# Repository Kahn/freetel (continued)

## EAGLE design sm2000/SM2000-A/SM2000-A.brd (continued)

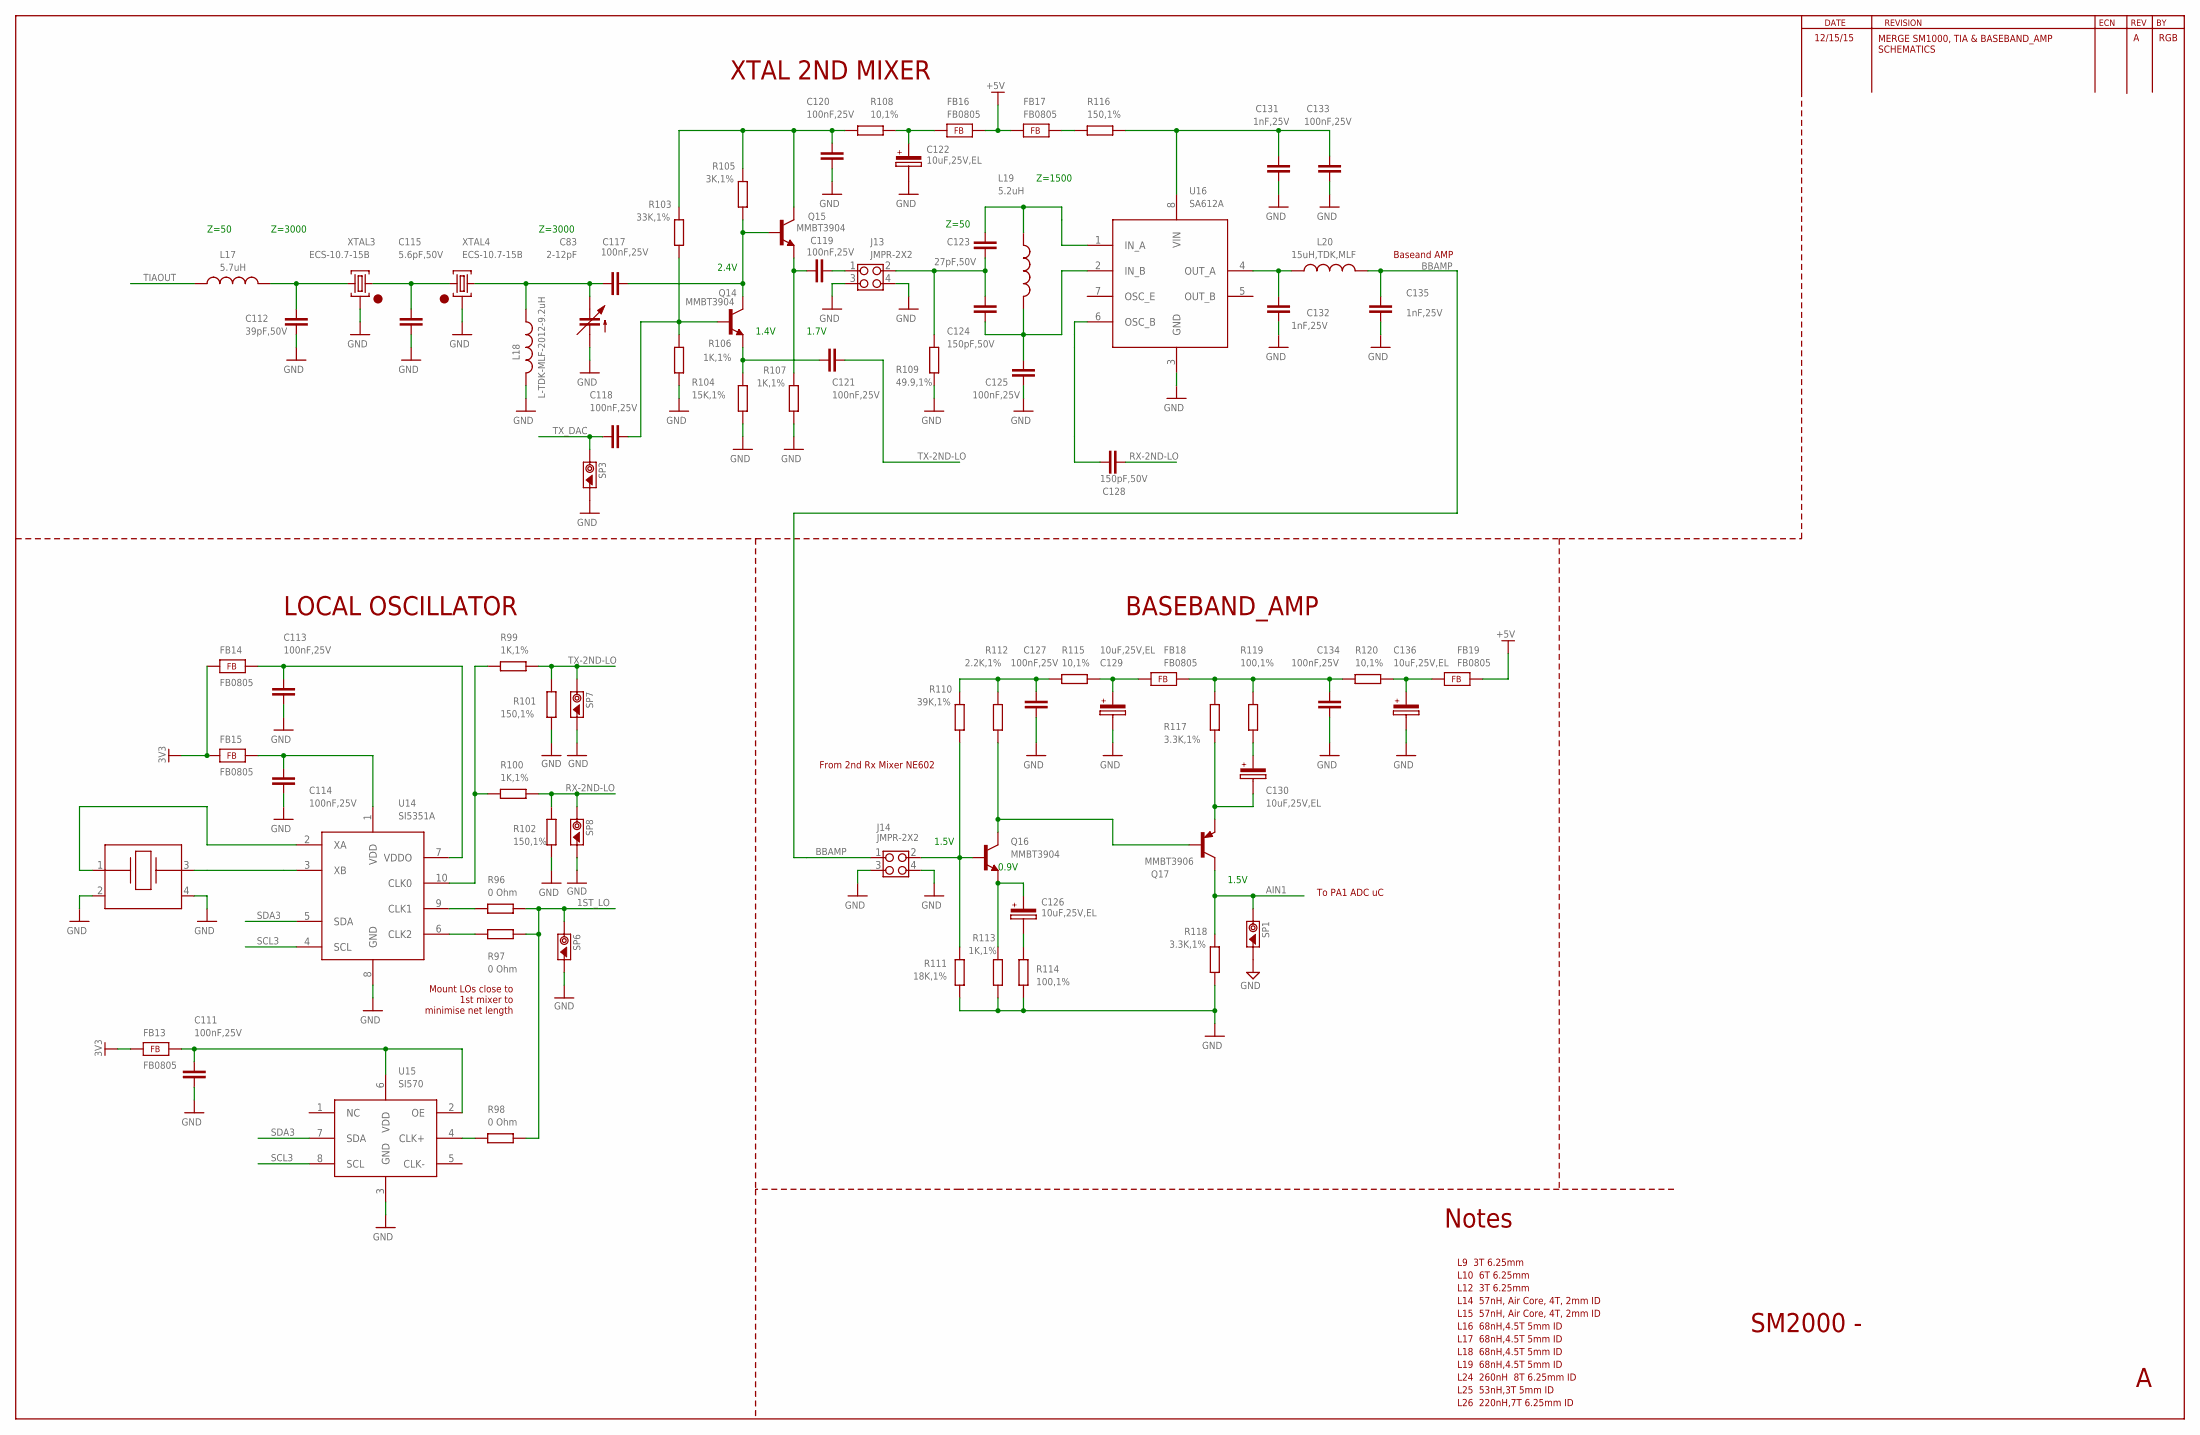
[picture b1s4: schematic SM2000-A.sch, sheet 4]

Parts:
C83: 2-12pF; TRIMCAP_VAR_2222_V
C111, C113, C114, C117, C118, C119, C120, C121, C125, C127, C133, C134: 100nF,25V; C0805
C112: 39pF,50V; C0805
C115: 5.6pF,50V; C0805
C122, C126, C129, C130, C136: 10uF,25V,EL; NICHICON-WJ-5
C123: 27pF,50V; C0805
C124, C128: 150pF,50V; C0805
C131, C132, C135: 1nF,25V; C0805
FB13, FB14, FB15, FB16, FB17, FB18, FB19: FB0805; FE0805
J13, J14: JMPR-2X2; JMPR-2X2X.1
L17: 5.7uH; L-TDK-MLF2012
L18: L-TDK-MLF-2012-9.2uH; L-TDK-MLF2012
L19: 5.2uH; L-TDK-MLF2012
L20: 15uH,TDK,MLF; L-TDK-MLF2012
Q14, Q15, Q16: MMBT3904; SOT23
Q17: MMBT3906; SOT23
R96, R97, R98: 0 Ohm; R0805
R99, R100, R106, R107, R113: 1K,1%; R0805
R101, R102, R116: 150,1%; R0805
R103: 33K,1%; R0805
R104: 15K,1%; R0805
R105: 3K,1%; R0805
R108, R115, R120: 10,1%; R0805
R109: 49.9,1%; R0805
R110: 39K,1%; R0805
R111: 18K,1%; R0805
R112: 2.2K,1%; R0805
R114, R119: 100,1%; R0805
R117, R118: 3.3K,1%; R0805
SP1, SP3, SP6, SP7, SP8: SCOPE_PAD
U14: SI5351A; MSOP10
U15: SI570
U16: SA612A; SO-08
XTAL2: 25.000MHz; CTS-405
XTAL3, XTAL4: ECS-10.7-15B; HC49U

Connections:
1ST_LO: R96.1, R97.1, R98.1, SP6.1; also elsewhere on the board
3V3: FB13.1, FB14.1, FB15.1; also elsewhere on the board
+5V: FB16.2, FB17.1, FB19.2; also elsewhere on the board
AIN1: Q17.3 (C), R118.2, SP1.1; also elsewhere on the board
BBAMP: C135.2, J14.1, L20.P$2 (2)
GND: C83.S, C111.2, C112.2, C113.2, C114.2, C115.2, C120.2, C122.2, C125.1, C127.2, C129.2, C131.1, C132.1, C133.1, C134.2, C135.1, C136.2, J13.3, J13.4, J14.3, J14.4, L18.P$2 (2), R101.2, R102.2, R104.1, R106.1, R107.1, R109.1, R111.1, R113.1, R114.1, R118.1, SP1.2, SP3.2, SP6.2, SP7.2, SP8.2, U14.8 (GND), U15.3 (GND), U16.3 (GND), XTAL2.2, XTAL2.4, XTAL3.2, XTAL4.2; also elsewhere on the board
unnamed: U14.2 (XA), XTAL2.1
unnamed: C119.2, J13.1
unnamed: C114.1, FB15.2, U14.1 (VDD)
unnamed: C123.1, C124.2, J13.2, R109.2
unnamed: C124.1, C125.2, L19.P$2 (2), U16.2 (IN_B)
unnamed: U14.3 (XB), XTAL2.3
unnamed: C126.1, Q16.2 (E), R113.2
unnamed: C134.1, FB18.2, R117.2, R119.2, R120.2
unnamed: C127.1, R110.2, R112.2, R115.2
unnamed: J14.2, Q16.1 (B), R110.1, R111.2
unnamed: Q16.3 (C), Q17.1 (B), R112.1
unnamed: C130.2, Q17.2 (E), R117.1
unnamed: C129.1, FB18.1, R115.1
unnamed: C126.2, R114.2
unnamed: C130.1, R119.1
unnamed: C136.1, FB19.1, R120.1
unnamed: C111.1, FB13.2, U15.2 (OE), U15.6 (VDD)
unnamed: C113.1, FB14.2, U14.7 (VDDO)
unnamed: R96.2, U14.9 (CLK1)
unnamed: R97.2, U14.6 (CLK2)
unnamed: R98.2, U15.4 (CLK+)
unnamed: R99.2, R100.2, U14.10 (CLK0)
unnamed: C120.1, Q15.3 (C), R103.2, R105.2, R108.2
unnamed: C117.2, Q14.3 (C), Q15.1 (B), R105.1
unnamed: C122.1, FB16.1, R108.1
unnamed: C112.1, L17.P$2 (2), XTAL3.3
unnamed: C115.1, XTAL3.1, XTAL4.1
unnamed: C83.R1 (R), C83.R2 (R), C117.1, L18.P$1 (1), XTAL4.3
unnamed: C118.1, Q14.1 (B), R103.1, R104.2
unnamed: C121.1, Q14.2 (E), R106.2
unnamed: C119.1, Q15.2 (E), R107.2
unnamed: C123.2, L19.P$1 (1), U16.1 (IN_A)
unnamed: FB17.2, R116.2
unnamed: C131.2, C133.2, R116.1, U16.8 (VIN)
unnamed: C128.2, U16.6 (OSC_B)
unnamed: C132.2, L20.P$1 (1), U16.4 (OUT_A)
RX-2ND-LO: C128.1, R100.1, R102.1, SP8.1
SCL3: U14.4 (SCL), U15.8 (SCL); also elsewhere on the board
SDA3: U14.5 (SDA), U15.7 (SDA); also elsewhere on the board
TIAOUT: L17.P$1 (1); also elsewhere on the board
TX-2ND-LO: C121.2, R99.1, R101.1, SP7.1
TX_DAC: C118.2, SP3.1; also elsewhere on the board

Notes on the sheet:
12/15/15
MERGE SM1000, TIA & BASEBAND_AMP SCHEMATICS
RGB
SM2000 -
L10 6T 6.25mm
L12 3T 6.25mm
L9 3T 6.25mm
L26 220nH,7T 6.25mm ID
L19 68nH,4.5T 5mm ID
L18 68nH,4.5T 5mm ID
L17 68nH,4.5T 5mm ID
L16 68nH,4.5T 5mm ID
L24 260nH 8T 6.25mm ID
L25 53nH,3T 5mm ID
L15 57nH, Air Core, 4T, 2mm ID
L14 57nH, Air Core, 4T, 2mm ID
1.7V
1.4V
2.4V
Z=50
Z=3000
Z=1500
Baseand AMP
XTAL 2ND MIXER
Notes
To PA1 ADC uC
From 2nd Rx Mixer NE602
1.5V
0.9V
BASEBAND_AMP
Mount LOs close to 1st mixer to minimise net length
LOCAL OSCILLATOR

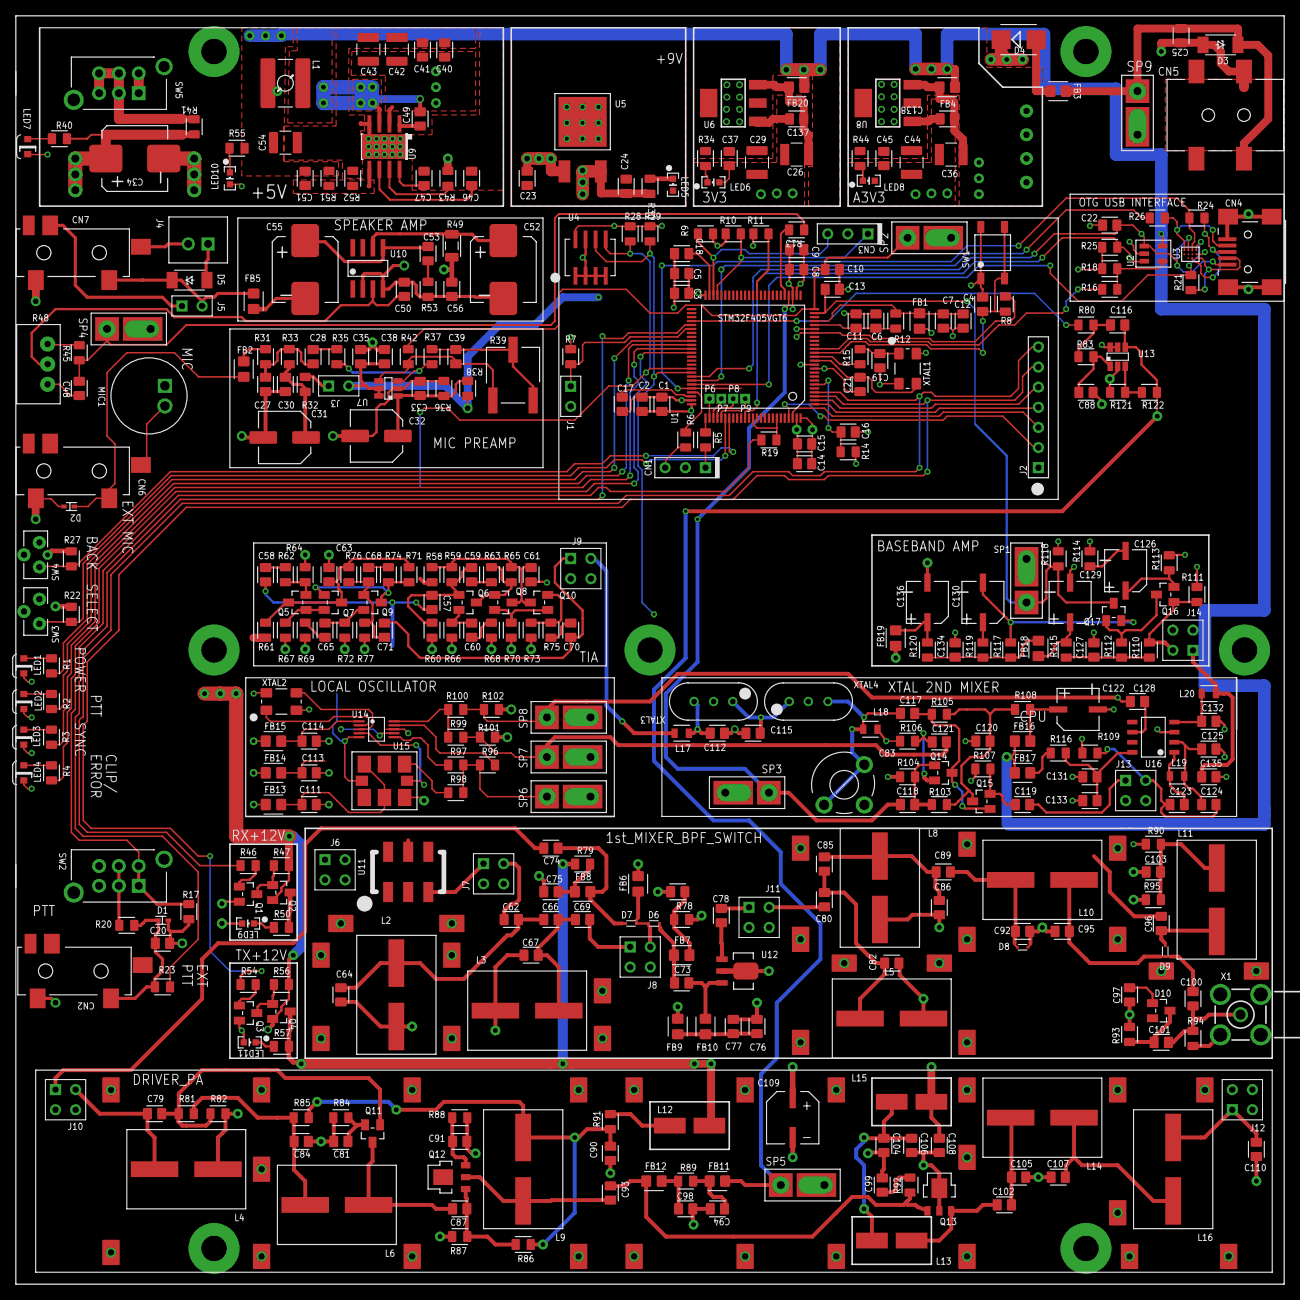
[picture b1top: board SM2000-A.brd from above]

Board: 4 copper layers, 160.0 x 160.0 mm, 452 parts (0 on the bottom side), 221 nets.

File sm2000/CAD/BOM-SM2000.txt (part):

Bill of Materials from SM2000.sch, 407 parts, grouped by values, as of 1/28/2016 6:16:19 PM

Part	Value			Device			Package
C1	100nF,25V		CAP-0805		C0805			
C3	100nF,25V		CAP-0805		C0805			
C4	100nF,25V		CAP-0805		C0805			
C8	100nF,25V		CAP-0805		C0805			
C11	100nF,25V		CAP-0805		C0805			
C12	100nF,25V		CAP-0805		C0805			
C14	100nF,25V		CAP-0805		C0805			
C20	100nF,25V		CAP-0805		C0805			
C24	100nF,25V		CAP-0805		C0805			
C30	100nF,25V		CAP-0805		C0805			
C33	100nF,25V		CAP-0805		C0805			
C35	100nF,25V		CAP-0805		C0805			
C37	100nF,25V		CAP-0805		C0805			
C41	100nF,25V		CAP-0805		C0805			
C45	100nF,25V		CAP-0805		C0805			
C48	100nF,25V		CAP-0805		C0805			
C49	100nF,25V		CAP-0805		C0805			
C56	100nF,25V		CAP-0805		C0805			
C57	100nF,25V		CAP-0805		C0805			
C58	100nF,25V		CAP-0805		C0805			
C59	100nF,25V		CAP-0805		C0805			
C60	100nF,25V		CAP-0805		C0805			
C61	100nF,25V		CAP-0805		C0805			
C63	100nF,25V		CAP-0805		C0805			
C65	100nF,25V		CAP-0805		C0805			
C68	100nF,25V		CAP-0805		C0805			
C70	100nF,25V		CAP-0805		C0805			
C71	100nF,25V		CAP-0805		C0805			
C137	100nF,25V		CAP-0805		C0805			
C138	100nF,25V		CAP-0805		C0805
C2	10nF,25V		CAP-0805		C0805			
C5	10nF,25V		CAP-0805		C0805			
C9	10nF,25V		CAP-0805		C0805			
C15	10nF,25V		CAP-0805		C0805			
C25	10nF,25V		CAP-0805		C0805
C6	1uF,25V			CAP-0805		C0805			
C7	1uF,25V			CAP-0805		C0805			
C77	1uF,25V			CAP-0805		C0805
C10	1nF,25V			CAP-0805		C0805			
C13	1nF,25V			CAP-0805		C0805			
C27	1nF,25V			CAP-0805		C0805			
C40	1nF,25V			CAP-0805		C0805			
C72	1nF,25V			CAP-0805		C0805			
C73	1nF,25V			CAP-0805		C0805			
C74	1nF,25V			CAP-0805		C0805			
C75	1nF,25V			CAP-0805		C0805			
C76	1nF,25V			CAP-0805		C0805			
C78	1nF,25V			CAP-0805		C0805			
C81	1nF,25V			CAP-0805		C0805			
C91	1nF,25V			CAP-0805		C0805			
C96	1nF,25V			CAP-0805		C0805			
C97	1nF,25V			CAP-0805		C0805			
C98	1nF,25V			CAP-0805		C0805			
C100	1nF,25V			CAP-0805		C0805			
C102	1nF,25V			CAP-0805		C0805			
C103	1nF,25V			CAP-0805		C0805			
C106	1nF,25V			CAP-0805		C0805			
C131	1nF,25V			CAP-0805		C0805			
C132	1nF,25V			CAP-0805		C0805			
C135	1nF,25V			CAP-0805		C0805
C16	1uF,16V			CAP-0805		C0805
C17	2.2uF,25V		CAP-0805		C0805			
C18	2.2uF,25V		CAP-0805		C0805			
C38	2.2uF,25V		CAP-0805		C0805
C19	20pF,50V		CAP-0805		C0805			
C21	20pF,50V		CAP-0805		C0805			
C51	20pF,50V		CAP-0805		C0805
C22	4.7uF,25V		CAP-0805		C0805
C23	.33uF,25V		CAP-0805		C0805
C26	22uF,25V		CAP-1210		C1210			
C29	22uF,25V		CAP-1210		C1210			
C36	22uF,25V		CAP-1210		C1210			
C42	22uF,25V		CAP-1210		C1210			
C43	22uF,25V		CAP-1210		C1210			
C44	22uF,25V		CAP-1210		C1210
C28	220nF,25V		CAP-0805		C0805
C31	100uF,6.3V,EL		NICHICON-WX-6.3		NICHICON-WX-6.3		
C32	100uF,6.3V,EL		NICHICON-WX-6.3		NICHICON-WX-6.3
C34	220uF,25V		CAP-CHEMI-MVE-HA0	CAP-CHEMI-HA0		
C52	220uF,25V		CAP-CHEMI-MVE-HA0	CAP-CHEMI-HA0		
C55	220uF,25V		CAP-CHEMI-MVE-HA0	CAP-CHEMI-HA0
C39	100pF,50V		CAP-0805		C0805
C46	470nF,25V		CAP-0805		C0805
C47	8.2nF,25V		CAP-0805		C0805
C50	3.9nF,25V		CAP-0805		C0805
C53	47nF,25V		CAP-0805		C0805
C54	22uF,25V,1210		CAPACITOR_1210		CAPC3225X168N
C62	3.3pF,50V		CAP-0805		C0805			
C69	3.3pF,50V		CAP-0805		C0805			
C80	3.3pF,50V		CAP-0805		C0805			
C89	3.3pF,50V		CAP-0805		C0805
C64	12pF.50V		CAP-0805		C0805
C66	0.5pF,50V		CAP-0805		C0805			
C85	0.5pF,50V		CAP-0805		C0805
C67	12pF,50V		CAP-0805		C0805			
C82	12pF,50V		CAP-0805		C0805			
C86	12pF,50V		CAP-0805		C0805
C79	22pF,50V		CAP-0805		C0805			
C92	22pF,50V		CAP-0805		C0805			
C93	22pF,50V		CAP-0805		C0805			
C95	22pF,50V		CAP-0805		C0805
C83	2.2pF,50V		CAP-0805		C0805			
C88	2.2pF,50V		CAP-0805		C0805
C84	0.1uF.25V		CAP-0805		C0805			
C90	0.1uF.25V		CAP-0805		C0805			
C94	0.1uF.25V		CAP-0805		C0805			
C104	0.1uF.25V		CAP-0805		C0805			
C108	0.1uF.25V		CAP-0805		C0805			
C125	0.1uF.25V		CAP-0805		C0805
C87	5.6pF,50V		CAP-0805		C0805			
C115	5.6pF,50V		CAP-0805		C0805
C99	1nF,25V,DNL		CAP-0805		C0805
C101	1pF,50V			CAP-0805		C0805
C105	33pF,50V		CAP-0805		C0805			
C110	33pF,50V		CAP-0805		C0805
C107	47pF,50V		CAP-0805		C0805
C109	100uF,25V,EL		CAP-CHEMI-F80		CAP-CHEMI-F80
C111	0.1uF,25V		CAP-0805		C0805			
C113	0.1uF,25V		CAP-0805		C0805			
C114	0.1uF,25V		CAP-0805		C0805			
C117	0.1uF,25V		CAP-0805		C0805			
C118	0.1uF,25V		CAP-0805		C0805			
C119	0.1uF,25V		CAP-0805		C0805			
C120	0.1uF,25V		CAP-0805		C0805			
C121	0.1uF,25V		CAP-0805		C0805			
C127	0.1uF,25V		CAP-0805		C0805			
C133	0.1uF,25V		CAP-0805		C0805			
C134	0.1uF,25V		CAP-0805		C0805
C112	39pF,50V		CAP-0805		C0805
C116	2-12pF			C-TRIMM3008		3008
C122	10uF,25V,EL		CAP-10UF-WJ5		NICHICON-WJ-5		
C126	10uF,25V,EL		CAP-10UF-WJ5		NICHICON-WJ-5		
C129	10uF,25V,EL		CAP-10UF-WJ5		NICHICON-WJ-5		
C130	10uF,25V,EL		CAP-10UF-WJ5		NICHICON-WJ-5		
C136	10uF,25V,EL		CAP-10UF-WJ5		NICHICON-WJ-5
C123	27pF,50V		CAP-0805		C0805
C124	150pF,50V		CAP-0805		C0805			
C128	150pF,50V		CAP-0805		C0805
CN1	HDR100-3		HDR100-3		HDR100-3		
CN3	HDR100-3		HDR100-3		HDR100-3
CN2	ST-3509			ST-3509			ST-3509			
CN6	ST-3509			ST-3509			ST-3509			
CN7	ST-3509			ST-3509			ST-3509
CN4	JS-MU3-002		JS-MU3-002		JI-MU3-002
CN5	DS-0518			DS-0518			DS-0518
D1	DNL			PESD5ZX			SOD523			
D2	DNL			PESD5ZX			SOD523
D3	PTVS20VP1UP		PTVS20VP1UP		SOD128
D4	BAT60J			BAT60J			SOD323R_INFINEON
D5	DNL			PTVS20VP1UP		SOD128
D6	BAR64-02V		BAR64-02V		SC79_INFINEON		
D7	BAR64-02V		BAR64-02V		SC79_INFINEON		
D8	BAR64-02V		BAR64-02V		SC79_INFINEON		
D9	BAR64-02V		BAR64-02V		SC79_INFINEON
D10	BAT18			BAT18			SOT23
FB1	FB0805			FB0805			FE0805			
FB2	FB0805			FB0805			FE0805			
FB3	FB0805			FB0805			FE0805			
FB4	FB0805			FB0805			FE0805			
FB5	FB0805			FB0805			FE0805			
FB6	FB0805			FB0805			FE0805			
FB7	FB0805			FB0805			FE0805			
FB8	FB0805			FB0805			FE0805			
FB9	FB0805			FB0805			FE0805			
FB10	FB0805			FB0805			FE0805			
FB11	FB0805			FB0805			FE0805			
FB12	FB0805			FB0805			FE0805			
FB13	FB0805			FB0805			FE0805			
FB14	FB0805			FB0805			FE0805			
FB15	FB0805			FB0805			FE0805			
FB16	FB0805			FB0805			FE0805			
FB17	FB0805			FB0805			FE0805			
FB18	FB0805			FB0805			FE0805			
FB19	FB0805			FB0805			FE0805			
FB20	FB0805			FB0805			FE0805
J1	JMP-2PIN		JMP-2PIN		JMPR-2PIN		
J3	JMP-2PIN		JMP-2PIN		JMPR-2PIN		
J5	JMP-2PIN		JMP-2PIN		JMPR-2PIN
J2	HDR100-7		HDR100-7		HDR100-7
J4	CONN-BOOM-XH-2A		CONN-BOOM-XH-2A		CONN-BOOM-XH-2A
J6	JMPR-2X2		JMPR-2X2		JMPR-2X2X.1		
J7	JMPR-2X2		JMPR-2X2		JMPR-2X2X.1		
J8	JMPR-2X2		JMPR-2X2		JMPR-2X2X.1		
J9	JMPR-2X2		JMPR-2X2		JMPR-2X2X.1		
J10	JMPR-2X2		JMPR-2X2		JMPR-2X2X.1		
J11	JMPR-2X2		JMPR-2X2		JMPR-2X2X.1		
J12	JMPR-2X2		JMPR-2X2		JMPR-2X2X.1		
J13	JMPR-2X2		JMPR-2X2		JMPR-2X2X.1		
J14	JMPR-2X2		JMPR-2X2		JMPR-2X2X.1
L1	4.2uH			SRR5028			SRR5028
L2	68nH			L-ROWE_15X10		L10X15			
L3	68nH			L-ROWE_15X10		L10X15			
L5	68nH			L-ROWE_15X10		L10X15			
L8	68nH			L-ROWE_15X10		L10X15
L4	57nH			L-ROWE_15X10		L10X15			
L14	57nH			L-ROWE_15X10		L10X15			
L16	57nH			L-ROWE_15X10		L10X15
L6	168nH			L-ROWE_15X10		L10X15
L7	260nH			L-US0204/5		0204/5
L9	54nH			L-ROWE_15X10		L10X15
L10	53nH 3T 5mm ID		L-ROWE_15X10		L10X15
L11	220nH			L-ROWE_15X10		L10X15
L12	RFC			RFC			Z15/4			
L13	RFC			RFC			Z15/4			
L15	RFC			RFC			Z15/4
L17	5.7uH			L-TDK-MLF-2012		L-TDK-MLF2012
L18	L-TDK-MLF-2012-9.2uH	L-TDK-MLF-2012		L-TDK-MLF2012
L19	5.2uH			L-TDK-MLF-2012		L-TDK-MLF2012
L20	15uH			L-TDK-MLF-2012		L-TDK-MLF2012
LED1	LTST-S220KGKT		LTST-S220K		LTST-S2200K		
LED3	LTST-S220KGKT		LTST-S220K		LTST-S2200K
LED2	LTST-S220KRKT		LTST-S220K		LTST-S2200K		
LED4	LTST-S220KRKT		LTST-S220K		LTST-S2200K
LED5	SML-LX0603GW		SML-LX0603SRW		SML-LX0603SRW		
LED6	SML-LX0603GW		SML-LX0603SRW		SML-LX0603SRW		
LED7	SML-LX0603GW		SML-LX0603SRW		SML-LX0603SRW		
LED8	SML-LX0603GW		SML-LX0603SRW		SML-LX0603SRW		
LED10	SML-LX0603GW		SML-LX0603SRW		SML-LX0603SRW
LED9	SML-LX0603SRW		SML-LX0603SRW		SML-LX0603SRW
LED11	SML-LX0603YW		SML-LX0603SRW		SML-LX0603SRW
MIC1	CMA-4544PF-W		CMA-4544PF-W		CMA-4544PF-W
P1	TPAD50			TPAD50			TPAD50			
P2	TPAD50			TPAD50			TPAD50			
P3	TPAD50			TPAD50			TPAD50			
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
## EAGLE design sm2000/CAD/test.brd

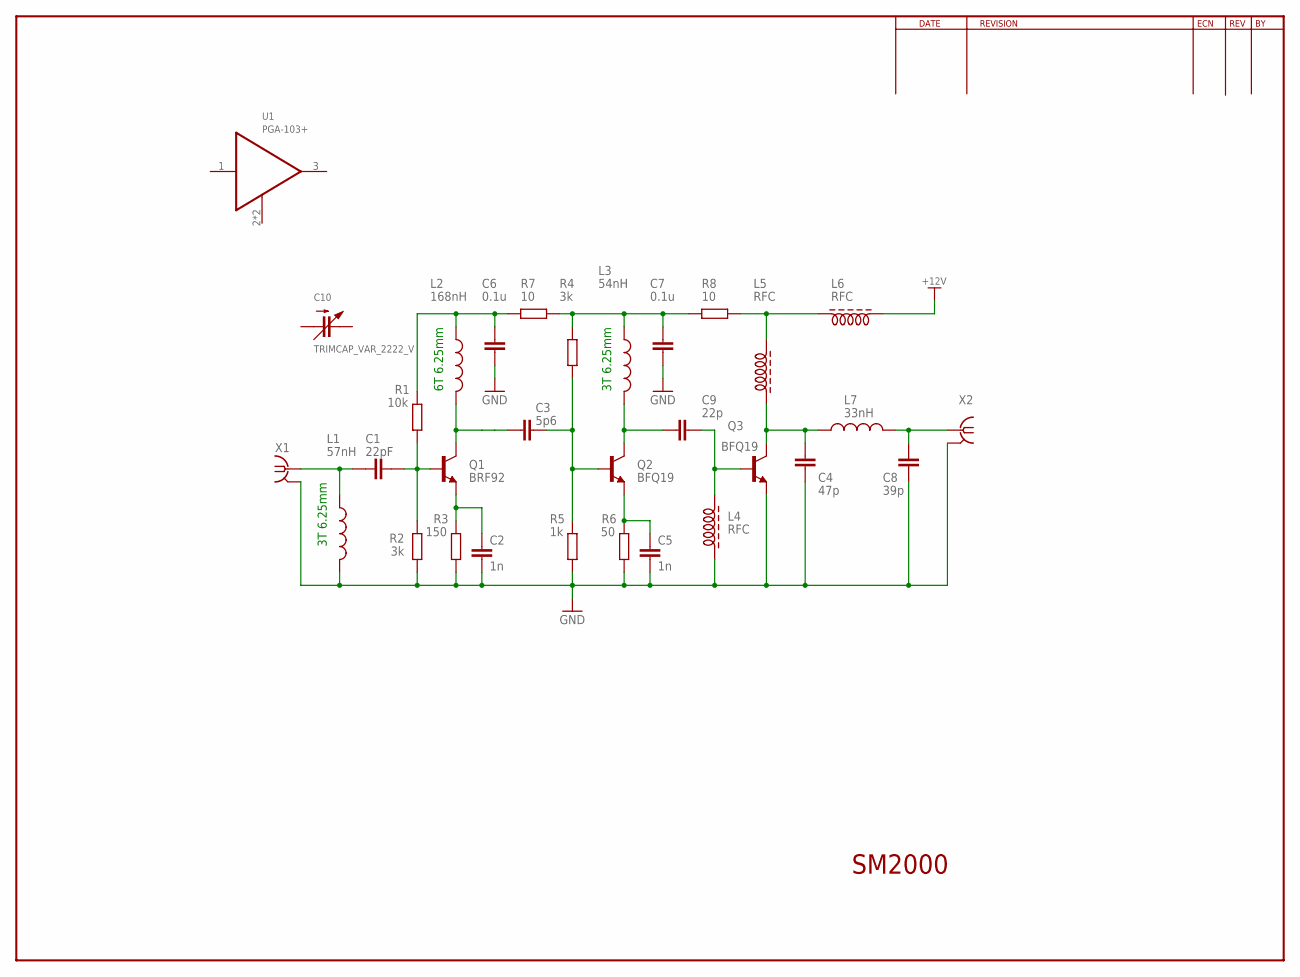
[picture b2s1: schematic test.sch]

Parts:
C1: 22pF; CAPC2012X145AN
C2, C5: 1n; C025-024X044
C3: 5p6; C025-024X044
C4: 47p; C025-024X044
C6, C7: 0.1u; C025-024X044
C8: 39p; C025-024X044
C9: 22p; C025-024X044
C10: TRIMCAP_VAR_2222_V
L1: 57nH; 0204/5
L2: 168nH; 0204/5
L3: 54nH; 0204/5
L4, L5, L6: RFC; Z15/4
L7: 33nH; 0204/5
Q1: BRF92; SOT23-EBC
Q2, Q3: BFQ19; SOT23-EBC
R1: 10k; RESC2012X70N
R2, R4: 3k; RESC2012X70N
R3: 150; RESC2012X70N
R5: 1k; RESC2012X70N
R6: 50; RESC2012X70N
R7, R8: 10; RESC2012X70N
U1: PGA-103+; DF782
X1, X2: BU-SMA-G

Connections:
+12V: L6.1
GND: C2.2, C4.2, C5.2, C6.2, C7.2, C8.2, L1.2, L4.1, Q3.E, R2.1, R3.1, R5.1, R6.1, X1.2, X1.3 (2), X1.4 (2), X1.5 (2), X2.2, X2.3 (2), X2.4 (2), X2.5 (2)
unnamed: C2.1, Q1.E, R3.2
unnamed: C1.2, L1.1, X1.1
unnamed: C1.1, Q1.B, R1.1, R2.2
unnamed: C5.1, Q2.E, R6.2
unnamed: C8.1, L7.2, X2.1
unnamed: L5.2, L6.2, R8.1
unnamed: C3.2, L2.2, Q1.C
unnamed: C6.1, L2.1, R1.2, R7.2
unnamed: C7.1, L3.1, R4.2, R7.1, R8.2
unnamed: C4.1, L5.1, L7.1, Q3.C
unnamed: C9.2, L3.2, Q2.C
unnamed: C3.1, Q2.B, R4.1, R5.2
unnamed: C9.1, L4.2, Q3.B

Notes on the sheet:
3T 6.25mm
6T 6.25mm
SM2000

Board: 2 copper layers, 31 parts (0 on the bottom side), 14 nets, no tracks yet.

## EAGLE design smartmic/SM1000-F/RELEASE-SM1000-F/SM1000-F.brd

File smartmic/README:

README for SM1000 Project
Rick Barnich KA8BMA and David Rowe VK5DGR 
14 August 2014

Introduction
------------

The SM1000 is an embedded hardware product that allows you to run
FreeDV without a PC. Just plug it into your SSB or FM radio, and you
now have Digital Voice (DV). It’s based on a STM32F4 micro-controller,
has a built in microphone, speaker amplifier, and transformer isolated
interfaces to your radio. It’s about the size of a smart phone, and
can be held in you hand and used like a regular PTT microphone, or sit
near your radio in a small box. SmartMic is slated for production
production in 2014 and will retail for US$195.

The SM1000 is open hardware (TAPR license) and runs open software
(LGPL license).

Notes
------

The original name for the project was SmartMic.  However as this name
is tradmarked in the USA we are now calling the project "the
SM1000".

The SM1000 schematic and PCB are design using Eagle.

The firmware lives in codec-dev/stm32.

Directories
-----------

doc         Documentation, use cases, block diagram, prototype assembly images
SM1000-A    First pass design that was never manufactured but used to collect
            review comment
SM1000-B    Prototype SM1000, small qty of PCBs made and hand loaded
SM1000-C    Beta SM1000. Changes to B to reflect testing / debug process.

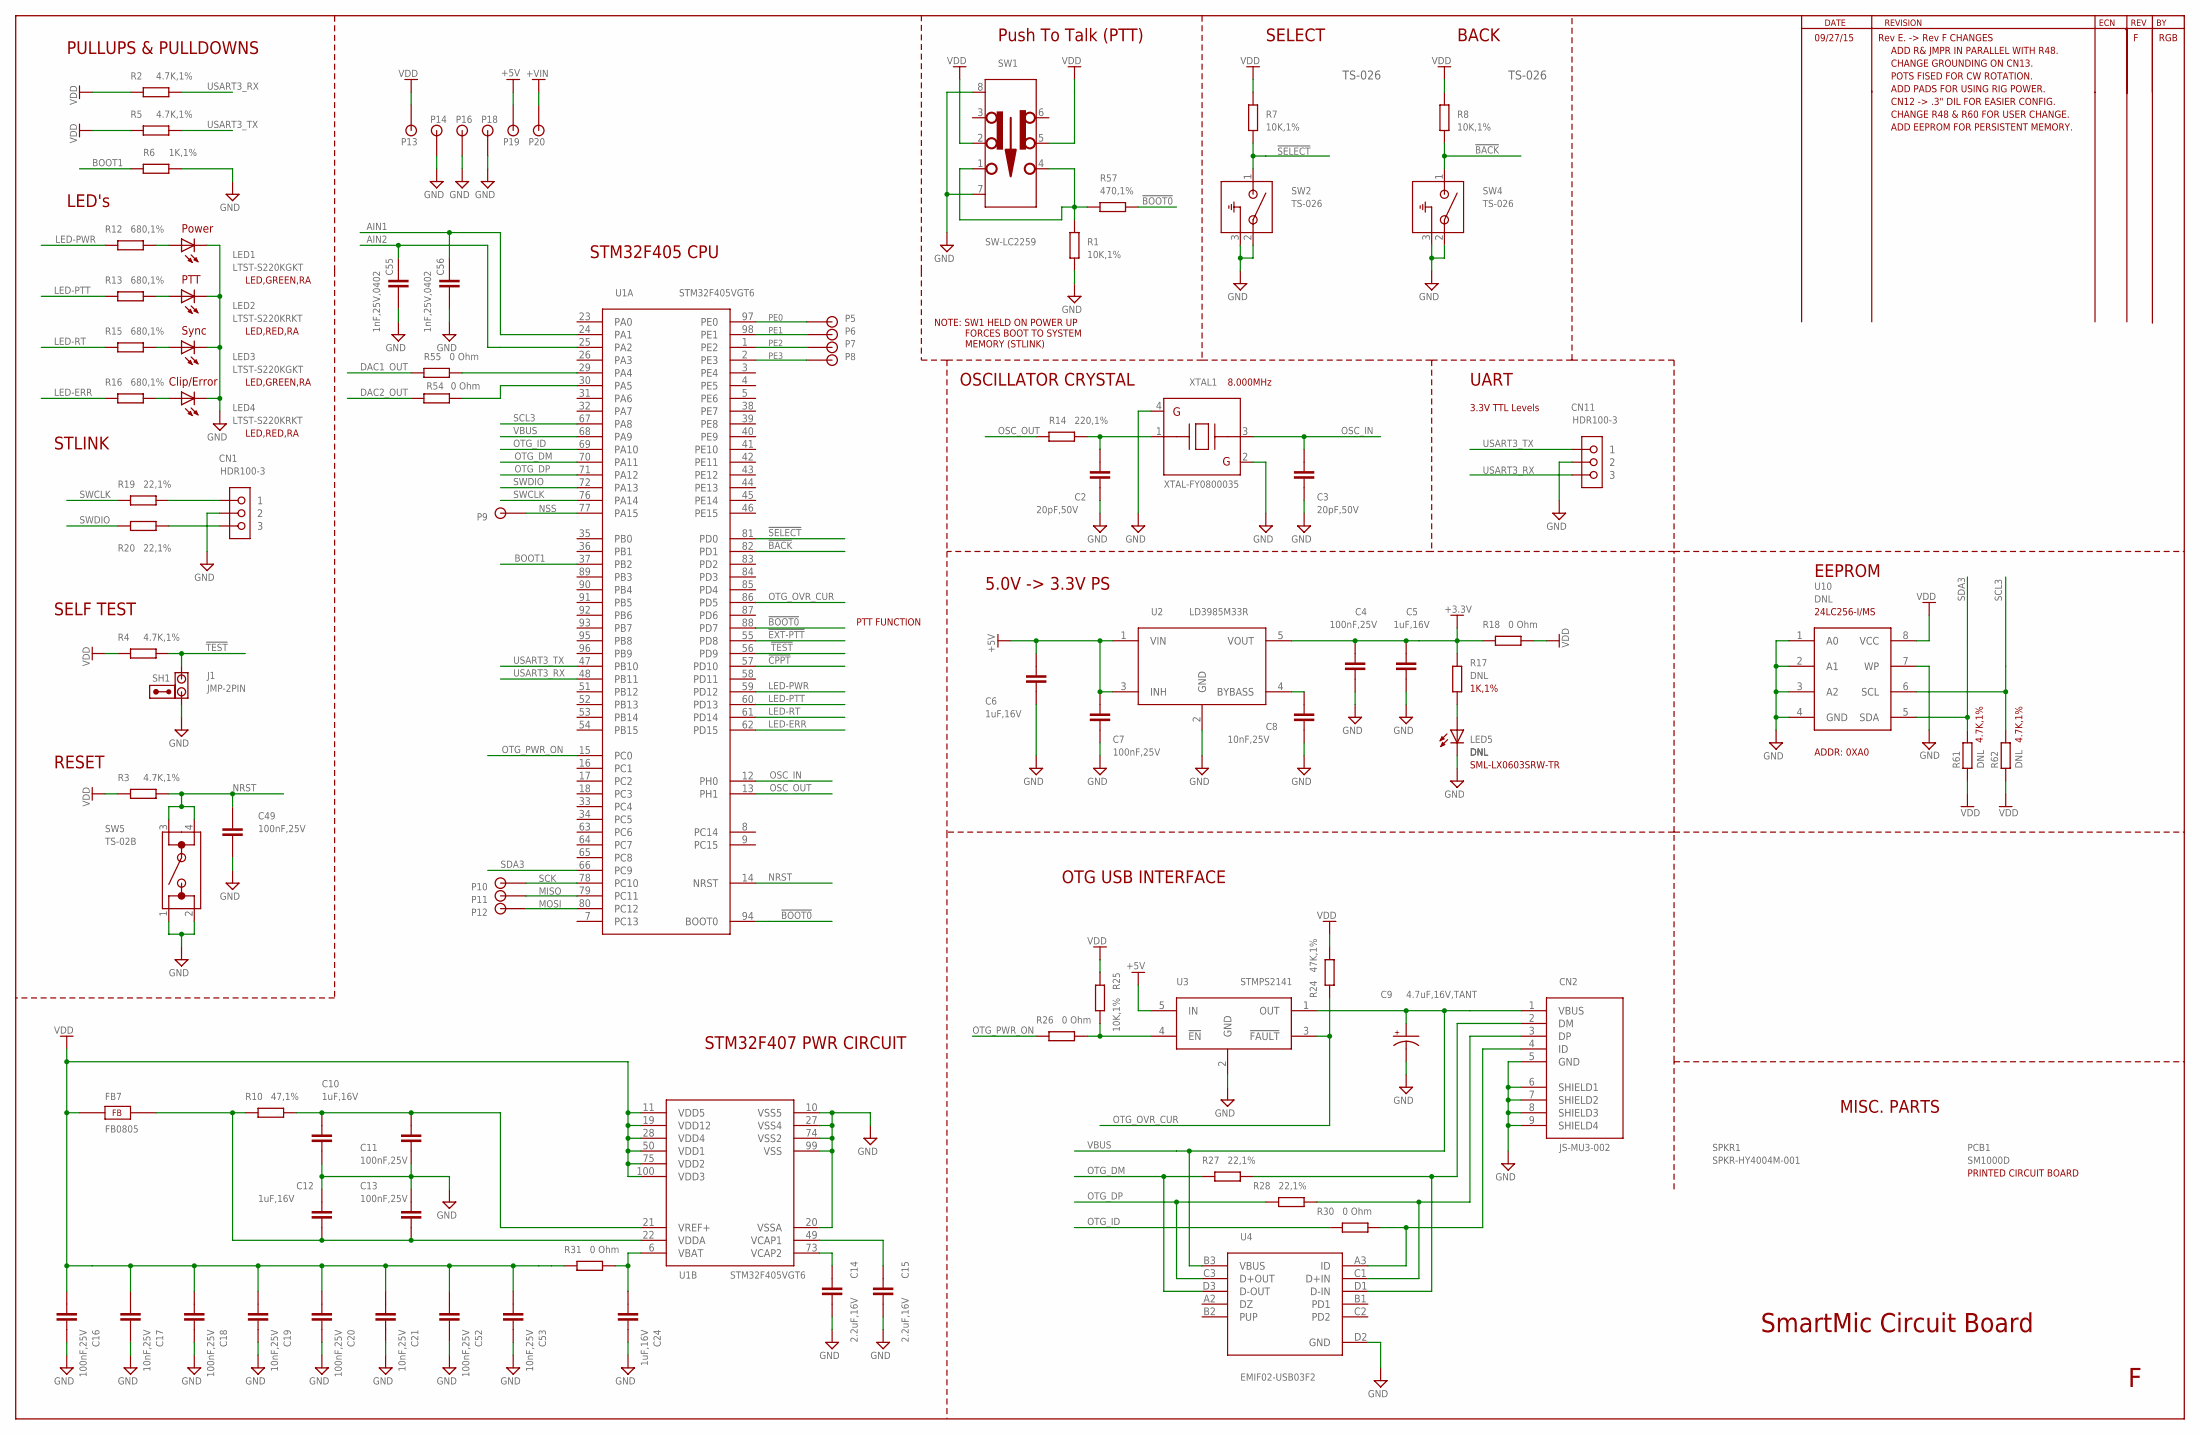
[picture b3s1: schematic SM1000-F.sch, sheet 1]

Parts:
C2, C3: 20pF,50V; CAPC1005X60N
C4, C7, C11, C13, C16, C18, C20, C49, C52: 100nF,25V; CAPC1005X60N
C5, C6, C10, C12, C24: 1uF,16V; CAPC1608X92N
C8, C17, C19, C21, C53: 10nF,25V; CAPC1005X60N
C9: 4.7uF,16V,TANT; C1206-TANT
C14, C15: 2.2uF,16V; CAPC1608X92N
C55, C56: 1nF,25V,0402; CAPC1005X60N
CN1, CN11: HDR100-3
CN2: JS-MU3-002; JI-MU3-002
FB7: FB0805; FE0805
J1: JMP-2PIN; JMPR-2PIN
LED1, LED3: LTST-S220KGKT; LTST-S2200K
LED2, LED4: LTST-S220KRKT; LTST-S2200K
LED5: DNL; SML-LX0603SRW
P5, P6, P7, P8, P9, P10, P11, P12, P13, P14, P16, P18, P19, P20: TPAD50
PCB1: SM1000D; NOPACKAGE
R1, R7, R8, R25: 10K,1%; RESC1005X40AN
R2, R3, R4, R5: 4.7K,1%; RESC1005X40AN
R6: 1K,1%; RESC1005X40AN
R10: 47,1%; RESC1608X55N
R12, R13, R15, R16: 680,1%; RESC1005X40AN
R14: 220,1%; RESC1005X40AN
R17: DNL; RESC1005X40AN
R18, R26, R30, R31, R54, R55: 0 Ohm; RESC1608X55N
R19, R20: 22,1%; RESC1608X55N
R24: 47K,1%; RESC1005X40AN
R27, R28: 22,1%; RESC1005X40AN
R57: 470,1%; RESC1005X40AN
R61, R62: DNL; RESC1608X55N
SH1: SHUNT,0.1IN; NOPACKAGE
SPKR1: SPKR-HY4004M-001; NOPACKAGE
SW1: SW-LC2259
SW2, SW4: TS-026
SW5: TS-02B
U1: STM32F405VGT6; LQFP100-14
U2: LD3985M33R; SOT23-5L
U3: STMPS2141; SOT23-5L
U4: EMIF02-USB03F2; ECOPACK-11
U10: DNL; SOIC8
XTAL1: XTAL-FY0800035

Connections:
!BACK!: R8.1, SW4.1, U1.82 (PD1)
!BOOT0!: R57.1, U1.88 (PD7), U1.94 (BOOT0)
!CPPT!: U1.57 (PD10); also elsewhere on the board
!EXT-PTT!: U1.55 (PD8); also elsewhere on the board
!SELECT!: R7.1, SW2.1, U1.81 (PD0)
!TEST!: J1.1, R4.2, U1.56 (PD9)
+3.3V: C4.1, C5.1, R17.2, R18.1, U2.5 (VOUT)
+5V: C6.1, C7.1, P19.1, U2.1 (VIN), U2.3 (INH), U3.5 (IN); also elsewhere on the board
+VIN: P20.1; also elsewhere on the board
AIN1: C56.1, U1.24 (PA1); also elsewhere on the board
AIN2: C55.1, U1.25 (PA2); also elsewhere on the board
BOOT1: R6.2, U1.37 (PB2)
DAC1_OUT: R55.2; also elsewhere on the board
DAC2_OUT: R54.2; also elsewhere on the board
GND: C2.2, C3.2, C4.2, C5.2, C6.2, C7.2, C8.2, C9.2, C10.2, C11.2, C12.2, C13.2, C14.2, C15.2, C16.2, C17.2, C18.2, C19.2, C20.2, C21.2, C24.2, C49.2, C52.2, C53.2, C55.2, C56.2, CN1.2, CN2.5 (GND), CN2.6 (SHIELD1), CN2.7 (SHIELD2), CN2.8 (SHIELD3), CN2.9 (SHIELD4), CN11.2, J1.2, LED1.C, LED2.C, LED3.C, LED4.C, LED5.C, P14.1, P16.1, P18.1, R1.1, R6.1, SW1.7, SW1.8, SW2.2, SW2.3, SW4.2, SW4.3, SW5.1, SW5.2, U1.10 (VSS5), U1.20 (VSSA), U1.27 (VSS4), U1.74 (VSS2), U1.99 (VSS), U2.2 (GND), U3.2 (GND), U4.D2 (GND), U10.1 (A0), U10.2 (A1), U10.3 (A2), U10.4 (GND), U10.7 (WP), XTAL1.2, XTAL1.4; also elsewhere on the board
LED-ERR: R16.1, U1.62 (PD15)
LED-PTT: R13.1, U1.60 (PD13)
LED-PWR: R12.1, U1.59 (PD12)
LED-RT: R15.1, U1.61 (PD14)
MISO: P11.1, U1.79 (PC11)
MOSI: P12.1, U1.80 (PC12)
unnamed: C14.1, U1.73 (VCAP2)
unnamed: C24.1, R31.2, U1.6 (VBAT)
unnamed: C15.1, U1.49 (VCAP1)
unnamed: C10.1, C11.1, R10.2, U1.21 (VREF+)
unnamed: C12.1, C13.1, FB7.2, R10.1, U1.22 (VDDA)
unnamed: CN1.3, R20.2
unnamed: CN1.1, R19.2
unnamed: C2.1, R14.2, XTAL1.1
unnamed: R55.1, U1.29 (PA4)
unnamed: C8.1, U2.4 (BYBASS)
unnamed: R54.1, U1.30 (PA5)
unnamed: R1.2, R57.2, SW1.1, SW1.4
unnamed: LED1.A, R12.2
unnamed: LED2.A, R13.2
unnamed: LED3.A, R15.2
unnamed: LED5.A, R17.1
unnamed: LED4.A, R16.2
unnamed: CN2.3 (DP), R28.1, U4.C1 (D+IN)
unnamed: CN2.2 (DM), R27.1, U4.D1 (D-IN)
unnamed: CN2.4 (ID), R30.1, U4.A3 (ID)
unnamed: R25.1, R26.2, U3.4 (!EN!)
NRST: C49.1, R3.2, SW5.3, SW5.4, U1.14 (NRST)
NSS: P9.1, U1.77 (PA15)
OSC_IN: C3.1, U1.12 (PH0), XTAL1.3
OSC_OUT: R14.1, U1.13 (PH1)
OTG_DM: R27.2, U1.70 (PA11), U4.D3 (D-OUT)
OTG_DP: R28.2, U1.71 (PA12), U4.C3 (D+OUT)
OTG_ID: R30.2, U1.69 (PA10)
OTG_OVR_CUR: R24.2, U1.86 (PD5), U3.3 (!FAULT!)
OTG_PWR_ON: R26.1, U1.15 (PC0)
PE0: P5.1, U1.97 (PE0)
PE1: P6.1, U1.98 (PE1)
PE2: P7.1, U1.1 (PE2)
PE3: P8.1, U1.2 (PE3)
SCK: P10.1, U1.78 (PC10)
SCL3: R62.2, U1.67 (PA8), U10.6 (SCL)
SDA3: R61.2, U1.66 (PC9), U10.5 (SDA)
SWCLK: R19.1, U1.76 (PA14)
SWDIO: R20.1, U1.72 (PA13)
USART3_RX: CN11.3, R2.2, U1.48 (PB11)
USART3_TX: CN11.1, R5.2, U1.47 (PB10)
VBUS: C9.1, CN2.1 (VBUS), U1.68 (PA9), U3.1 (OUT), U4.B3 (VBUS)
VDD: C16.1, C17.1, C18.1, C19.1, C20.1, C21.1, C52.1, C53.1, FB7.1, P13.1, R2.1, R3.1, R4.1, R5.1, R7.2, R8.2, R18.2, R24.1, R25.2, R31.1, R61.1, R62.1, SW1.2, SW1.5, U1.11 (VDD5), U1.19 (VDD12), U1.28 (VDD4), U1.50 (VDD1), U1.75 (VDD2), U1.100 (VDD3), U10.8 (VCC); also elsewhere on the board

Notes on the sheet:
PULLUPS & PULLDOWNS
LED's
STLINK
OSCILLATOR CRYSTAL
5.0V -> 3.3V PS
OTG USB INTERFACE
STM32F405 CPU
STM32F407 PWR CIRCUIT
SmartMic Circuit Board
Push To Talk (PTT)
PTT FUNCTION
NOTE: SW1 HELD ON POWER UP FORCES BOOT TO SYSTEM MEMORY (STLINK)
SELF TEST
RESET
SELECT
BACK
Power
PTT
Sync
Clip/Error
UART
3.3V TTL Levels
8.000MHz
TS-026
RGB
MISC. PARTS
LED,GREEN,RA
LED,RED,RA
1K,1%
SML-LX0603SRW-TR
DNL
EEPROM
ADDR: 0XA0
09/27/15
Rev E. -> Rev F CHANGES
ADD R& JMPR IN PARALLEL WITH R48.
CHANGE GROUNDING ON CN13.
POTS FISED FOR CW ROTATION.
ADD PADS FOR USING RIG POWER.
CN12 -> .3" DIL FOR EASIER CONFIG.
